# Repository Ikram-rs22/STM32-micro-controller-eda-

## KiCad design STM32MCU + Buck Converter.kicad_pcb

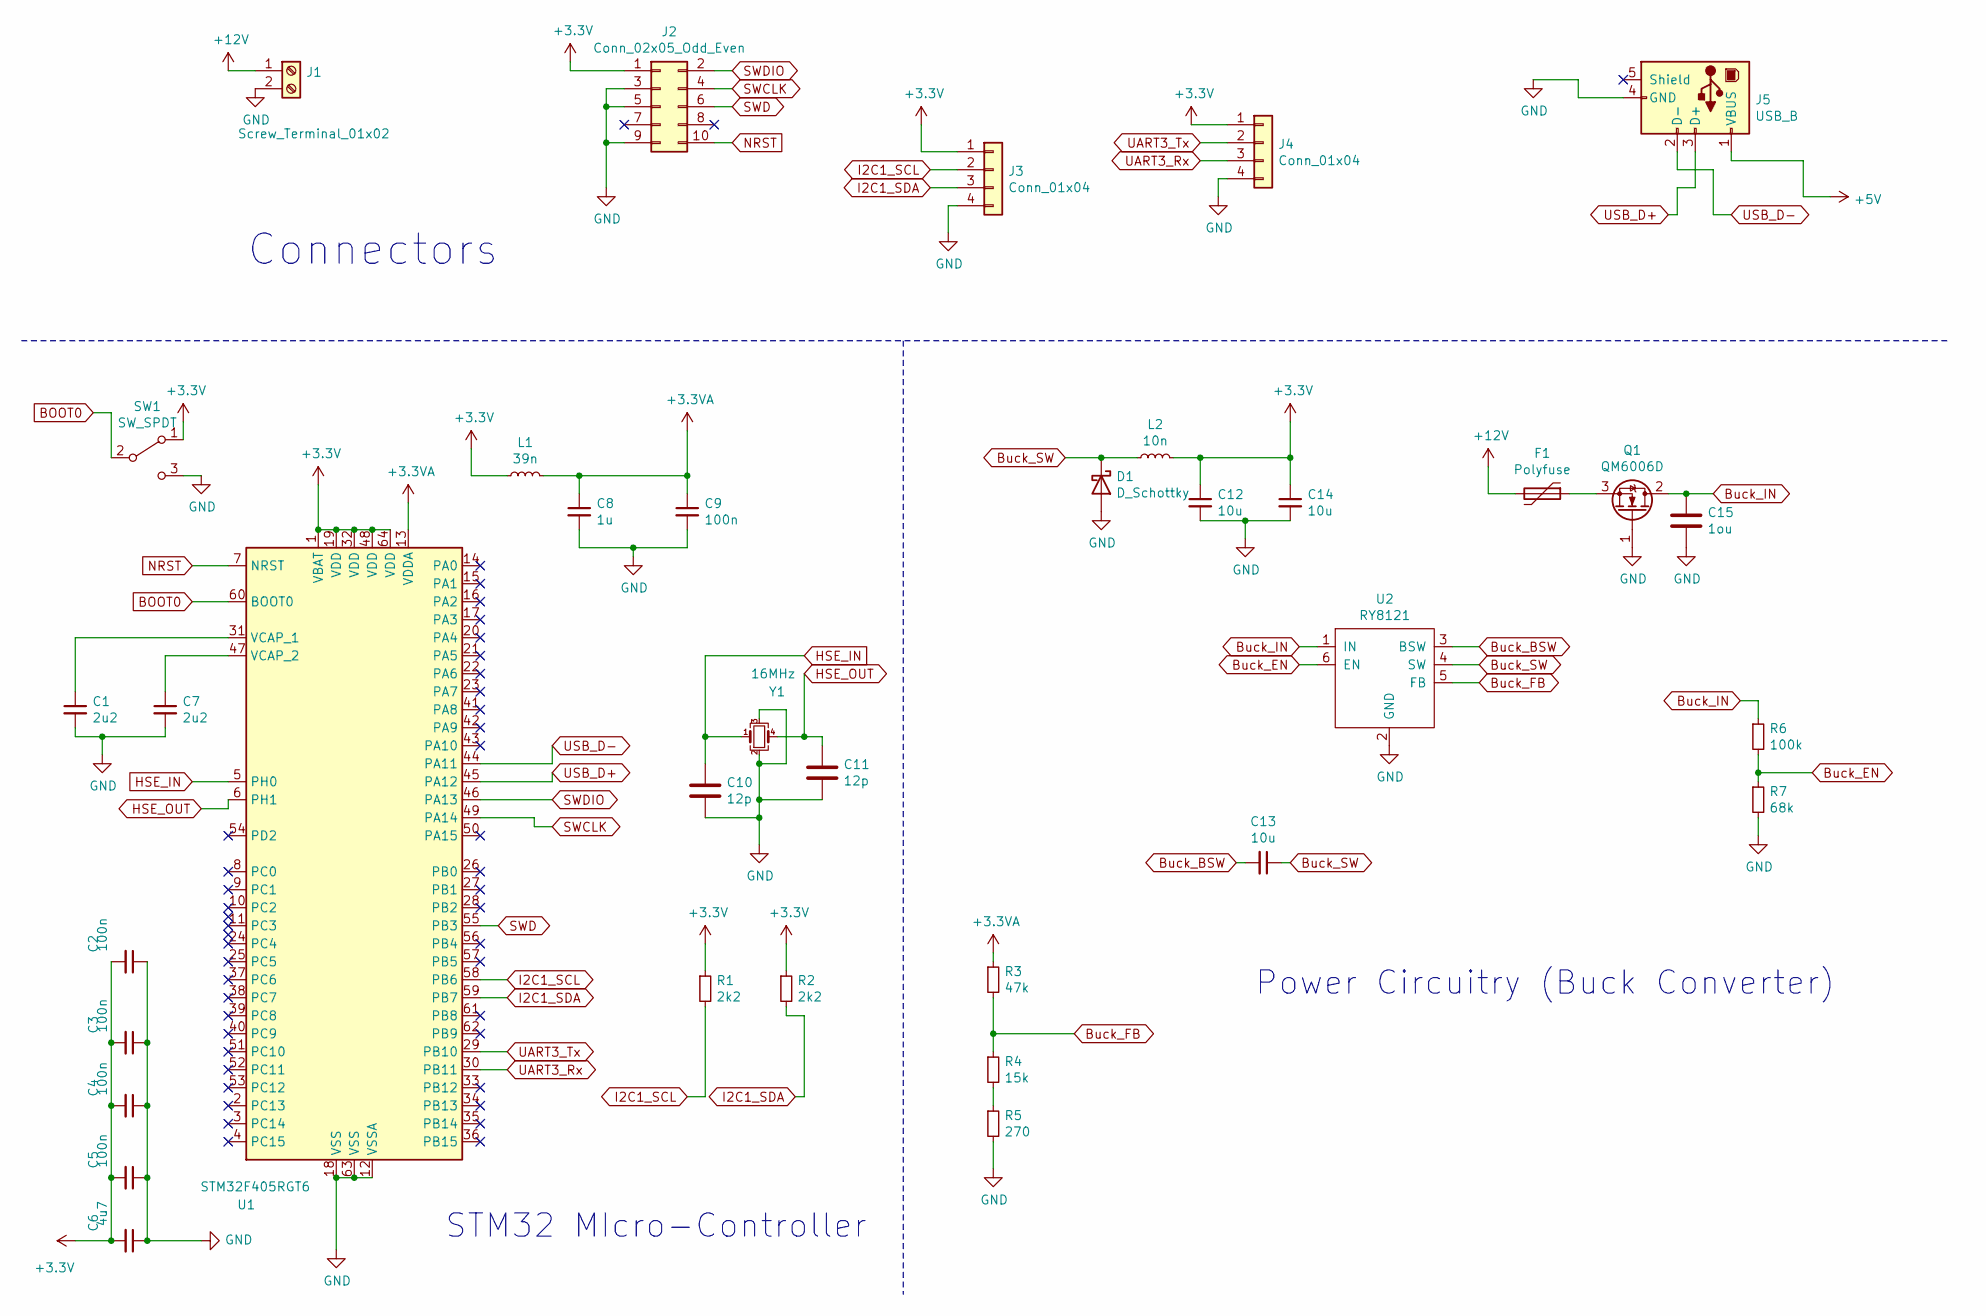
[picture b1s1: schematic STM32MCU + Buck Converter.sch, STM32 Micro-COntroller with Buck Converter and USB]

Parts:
C1: 2u2; C_2225_5664Metric_Pad1.80x6.60mm_HandSolder
C2, C3, C4, C5: 100n; C_0805_2012Metric
C6: 4u7; C_3640_9110Metric_Pad2.10x10.45mm_HandSolder
C7: 2u2; C_3640_9110Metric_Pad2.10x10.45mm_HandSolder
C8: 1u; C_0201_0603Metric
C9: 100n; C_0201_0603Metric
C10, C11: 12p; C_0805_2012Metric
C12, C13: 10u; C_0805_2012Metric
C14: 10u; C_3640_9110Metric_Pad2.10x10.45mm_HandSolder
C15: 1ou; C_3640_9110Metric_Pad2.10x10.45mm_HandSolder
D1: D_Schottky; D_SOD-110
F1: Polyfuse; Fuse_Bourns_MF-RG1100
J1: Screw_Terminal_01x02; TerminalBlock_4Ucon_1x02_P3.50mm_Vertical
J2: Conn_02x05_Odd_Even; PinHeader_2x05_P2.00mm_Horizontal
J3, J4: Conn_01x04; FanPinHeader_1x04_P2.54mm_Vertical
J5: USB_B; USB_Micro-B_Molex-105017-0001
L1: 39n; L_TDK_SLF6025
L2: 10n; L_TDK_SLF6025
Q1: QM6006D; TO-252-2
R1, R2: 2k2; R_Axial_DIN0411_L9.9mm_D3.6mm_P12.70mm_Horizontal
R3: 47k; R_Axial_DIN0411_L9.9mm_D3.6mm_P12.70mm_Horizontal
R4: 15k; R_Axial_DIN0411_L9.9mm_D3.6mm_P12.70mm_Horizontal
R5: 270; R_Axial_DIN0411_L9.9mm_D3.6mm_P12.70mm_Horizontal
R6: 100k; R_Axial_DIN0411_L9.9mm_D3.6mm_P12.70mm_Horizontal
R7: 68k; R_Axial_DIN0411_L9.9mm_D3.6mm_P12.70mm_Horizontal
SW1: SW_SPDT; SW_SPDT_PCM12
U1: STM32F405RGT6; LQFP-64_10x10mm_P0.5mm
U2: RY8121; SOT-23-6
Y1: 16MHz; Crystal_SMD_0603-4Pin_6.0x3.5mm

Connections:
+3.3VA: C8.1, C9.1, L1.2, R3.1, U1.13 (VDDA)
+3V3: C2.2, C3.2, C4.2, C5.2, C6.2, C12.1, C14.1, J2.1, J3.1, J4.1, L1.1, L2.2, R1.1, R2.1, SW1.1 (A), U1.1 (VBAT), U1.19 (VDD), U1.32 (VDD), U1.48 (VDD), U1.64 (VDD)
+5V: J5.1 (VBUS)
+12V: F1.2, J1.1
BOOT0: SW1.2 (B), U1.60 (BOOT0)
Buck_BSW: C13.2, U2.3 (BSW)
Buck_EN: R6.2, R7.1, U2.6 (EN)
Buck_FB: R3.2, R4.1, U2.5 (FB)
Buck_IN: C15.1, Q1.2 (D), R6.1, U2.1 (IN)
Buck_SW: C13.1, D1.1 (K), L2.1, U2.4 (SW)
GND: C1.2, C2.1, C3.1, C4.1, C5.1, C6.1, C7.2, C8.2, C9.2, C10.2, C11.2, C12.2, C14.2, C15.2, D1.2 (A), J1.2, J2.3, J2.5, J2.9, J3.4, J4.4, J5.4 (GND), Q1.1 (G), R5.2, R7.2, SW1.3 (C), U1.12 (VSSA), U1.18 (VSS), U1.63 (VSS), U2.2 (GND), Y1.2, Y1.3
HSE_IN: C10.1, U1.5 (PH0), Y1.1
HSE_OUT: C11.1, U1.6 (PH1), Y1.4
I2C1_SCL: J3.2, R1.2, U1.58 (PB6)
I2C1_SDA: J3.3, R2.2, U1.59 (PB7)
NRST: J2.10, U1.7 (NRST)
unnamed: C1.1, U1.31 (VCAP_1)
unnamed: C7.1, U1.47 (VCAP_2)
unnamed: F1.1, Q1.3 (S)
unnamed: R4.2, R5.1
SWCLK: J2.4, U1.49 (PA14)
SWD: J2.6, U1.55 (PB3)
SWDIO: J2.2, U1.46 (PA13)
UART3_Rx: J4.3, U1.30 (PB11)
UART3_Tx: J4.2, U1.29 (PB10)
USB_D+: J5.3 (D+), U1.45 (PA12)
USB_D-: J5.2 (D-), U1.44 (PA11)

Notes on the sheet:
STM32 MIcro-Controller
Power Circuitry (Buck Converter)
Connectors

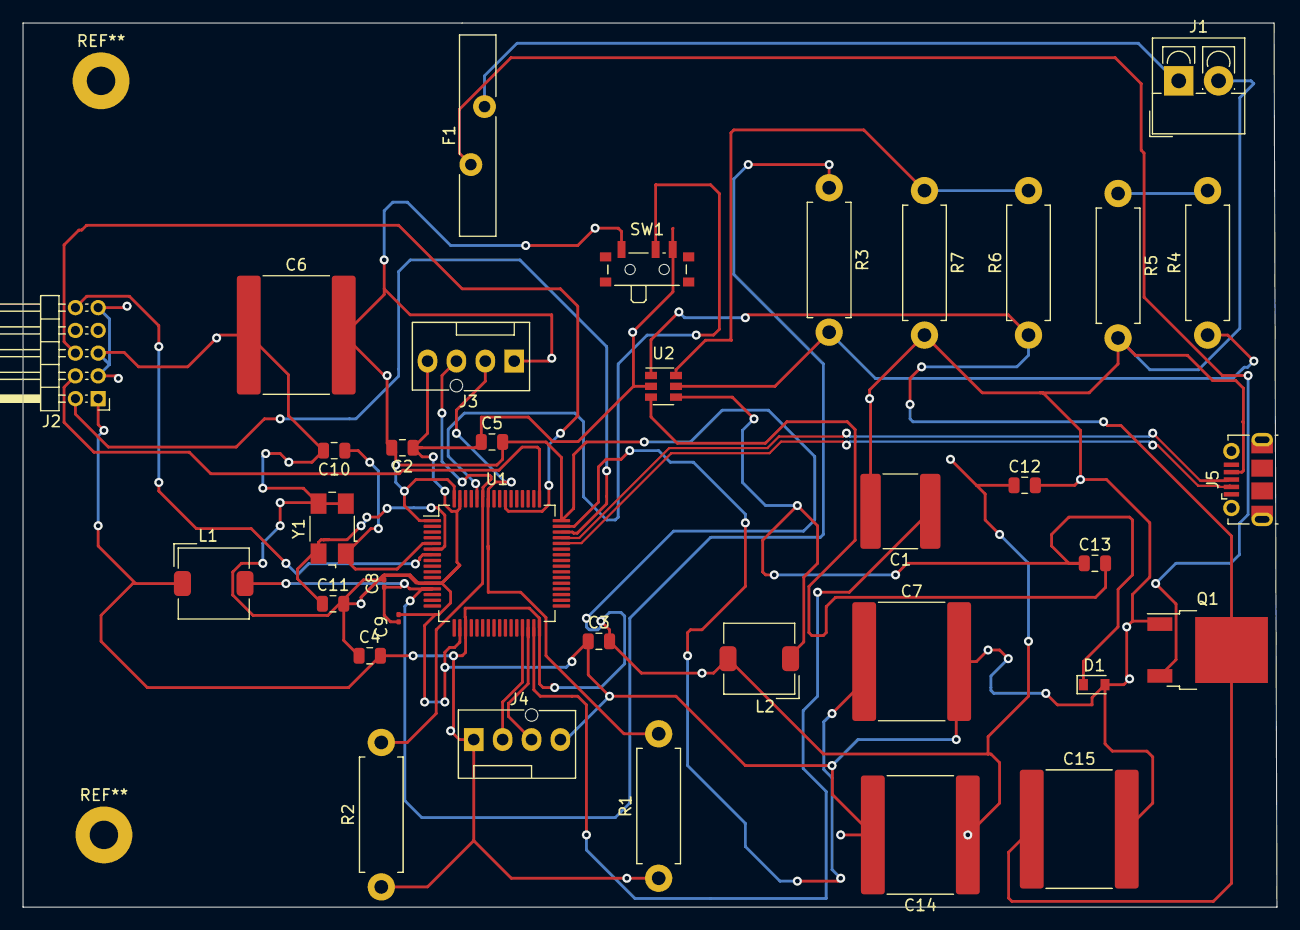
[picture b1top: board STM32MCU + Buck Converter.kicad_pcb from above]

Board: 4 copper layers, 110.2 x 77.7 mm, 36 parts (0 on the bottom side), 26 nets.

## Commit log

2021-03-02 schematic
2021-03-02 pcb design
2021-03-02 Gerber files
